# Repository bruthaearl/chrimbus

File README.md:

# chrimbus
## chrimbus tree ornamets for the family

More details on my [blog](http://www.oakst.io)

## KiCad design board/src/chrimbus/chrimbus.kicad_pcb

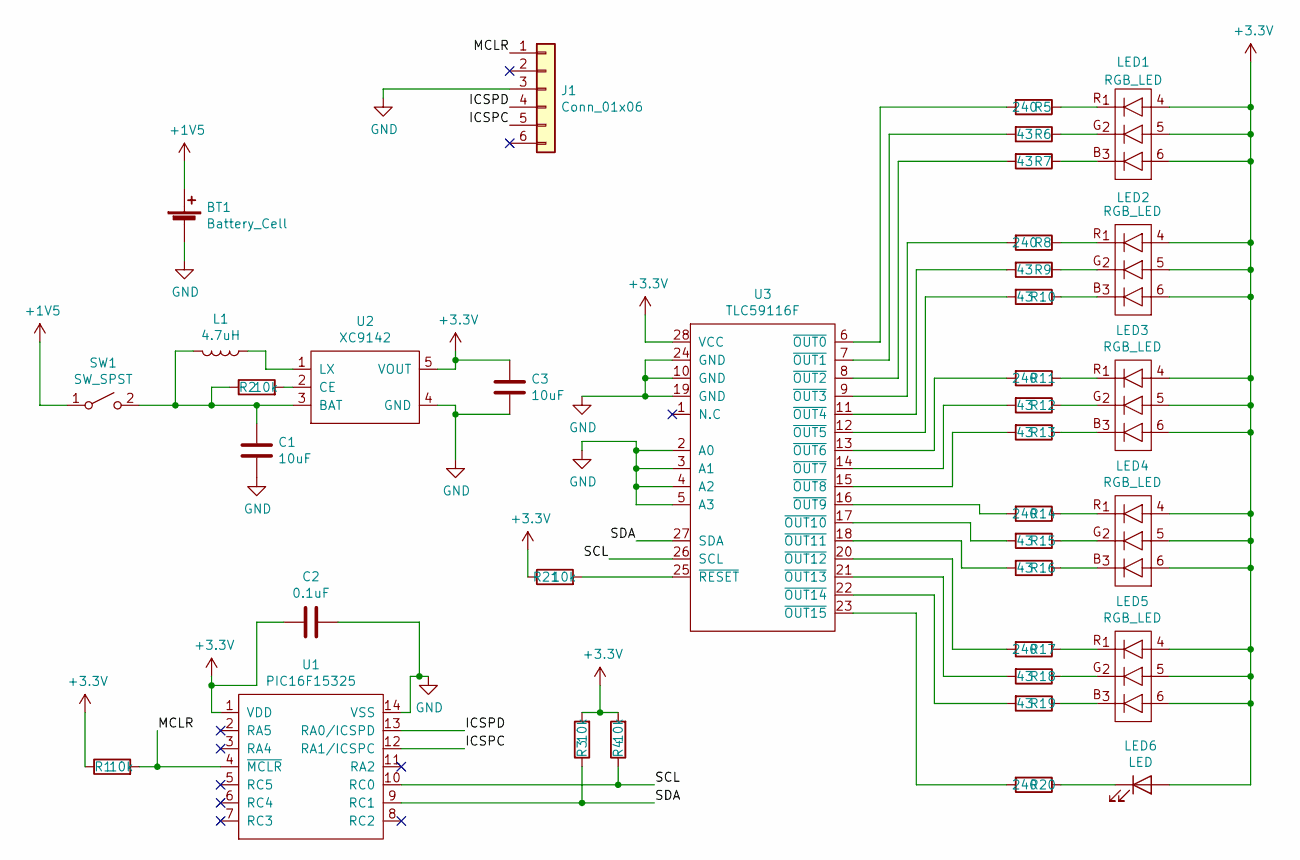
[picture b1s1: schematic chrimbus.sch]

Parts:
BT1: Battery_Cell; BCAAAPC
C1, C3: 10uF; C_0805_2012Metric
C2: 0.1uF; C_0805_2012Metric
J1: Conn_01x06; Tag Connect
L1: 4.7uH; L_0805_2012Metric_Pad1.15x1.40mm_HandSolder
LED1, LED2, LED3, LED4, LED5: RGB_LED; APF3236LSEEZGKQBKC
LED6: LED; LTST-C150AKT
R1, R2, R3, R4, R21: 10k; R_0603_1608Metric
R5, R8, R11, R14, R17, R20: 240; R_0603_1608Metric
R6, R7, R9, R10, R12, R13, R15, R16, R18, R19: 43; R_0603_1608Metric
SW1: SW_SPST; GF-123-0054
U1: PIC16F15325; TSSOP-14_4.4x5mm_P0.65mm
U2: XC9142; SOT-23-5_HandSoldering
U3: TLC59116F; TSSOP-28_4.4x9.7mm_P0.65mm

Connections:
+1V5: BT1.1 (+), SW1.1 (A)
+3V3: C2.2, C3.2, LED1.4, LED1.5, LED1.6, LED2.4, LED2.5, LED2.6, LED3.4, LED3.5, LED3.6, LED4.4, LED4.5, LED4.6, LED5.4, LED5.5, LED5.6, LED6.2 (A), R1.1, R3.2, R4.2, R21.1, U1.1 (VDD), U2.5 (VOUT), U3.28 (VCC); also elsewhere on the board
/ICSPC: J1.5, U1.12 (RA1/ICSPC)
/ICSPD: J1.4, U1.13 (RA0/ICSPD)
/MCLR: J1.1, R1.2, U1.4 (~MCLR)
/SCL: R4.1, U1.10 (RC0), U3.26 (SCL)
/SDA: R3.1, U1.9 (RC1), U3.27 (SDA)
GND: BT1.2 (-), C1.1, C2.1, C3.1, J1.3, U1.14 (VSS), U2.4 (GND), U3.2 (A0), U3.3 (A1), U3.4 (A2), U3.5 (A3), U3.10 (GND), U3.19 (GND), U3.24 (GND); also elsewhere on the board
unnamed: C1.2, L1.2, R2.1, SW1.2 (B), U2.3 (BAT)
unnamed: L1.1, U2.1 (LX)
unnamed: LED1.1, R5.1
unnamed: LED1.2, R6.1
unnamed: LED1.3, R7.1
unnamed: LED2.1, R8.1
unnamed: LED2.2, R9.1
unnamed: LED2.3, R10.1
unnamed: LED3.1, R11.1
unnamed: LED3.2, R12.1
unnamed: LED3.3, R13.1
unnamed: LED4.1, R14.1
unnamed: LED4.2, R15.1
unnamed: LED4.3, R16.1
unnamed: LED5.1, R17.1
unnamed: LED5.2, R18.1
unnamed: LED5.3, R19.1
unnamed: LED6.1 (K), R20.1
unnamed: R2.2, U2.2 (CE)
unnamed: R5.2, U3.6 (~OUT0)
unnamed: R6.2, U3.7 (~OUT1)
unnamed: R7.2, U3.8 (~OUT2)
unnamed: R8.2, U3.9 (~OUT3)
unnamed: R9.2, U3.11 (~OUT4)
unnamed: R10.2, U3.12 (~OUT5)
unnamed: R11.2, U3.13 (~OUT6)
unnamed: R12.2, U3.14 (~OUT7)
unnamed: R13.2, U3.15 (~OUT8)
unnamed: R14.2, U3.16 (~OUT9)
unnamed: R15.2, U3.17 (~OUT10)
unnamed: R16.2, U3.18 (~OUT11)
unnamed: R17.2, U3.20 (~OUT12)
unnamed: R18.2, U3.21 (~OUT13)
unnamed: R19.2, U3.22 (~OUT14)
unnamed: R20.2, U3.23 (~OUT15)
unnamed: R21.2, U3.25 (~RESET)

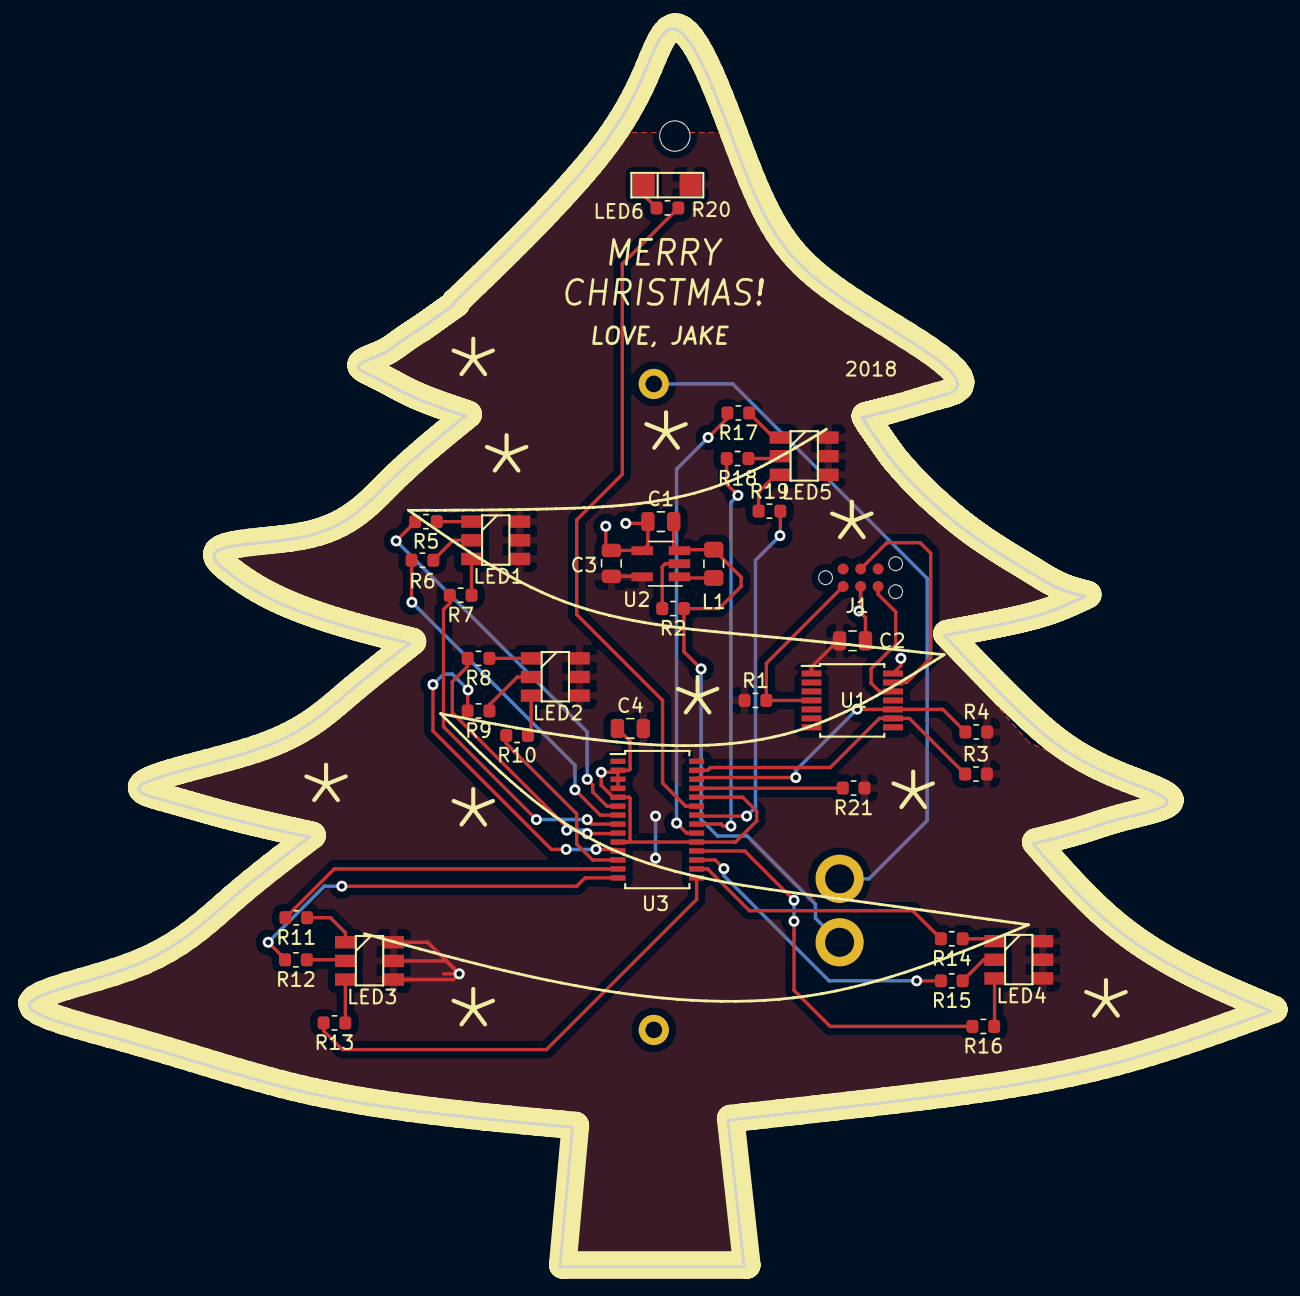
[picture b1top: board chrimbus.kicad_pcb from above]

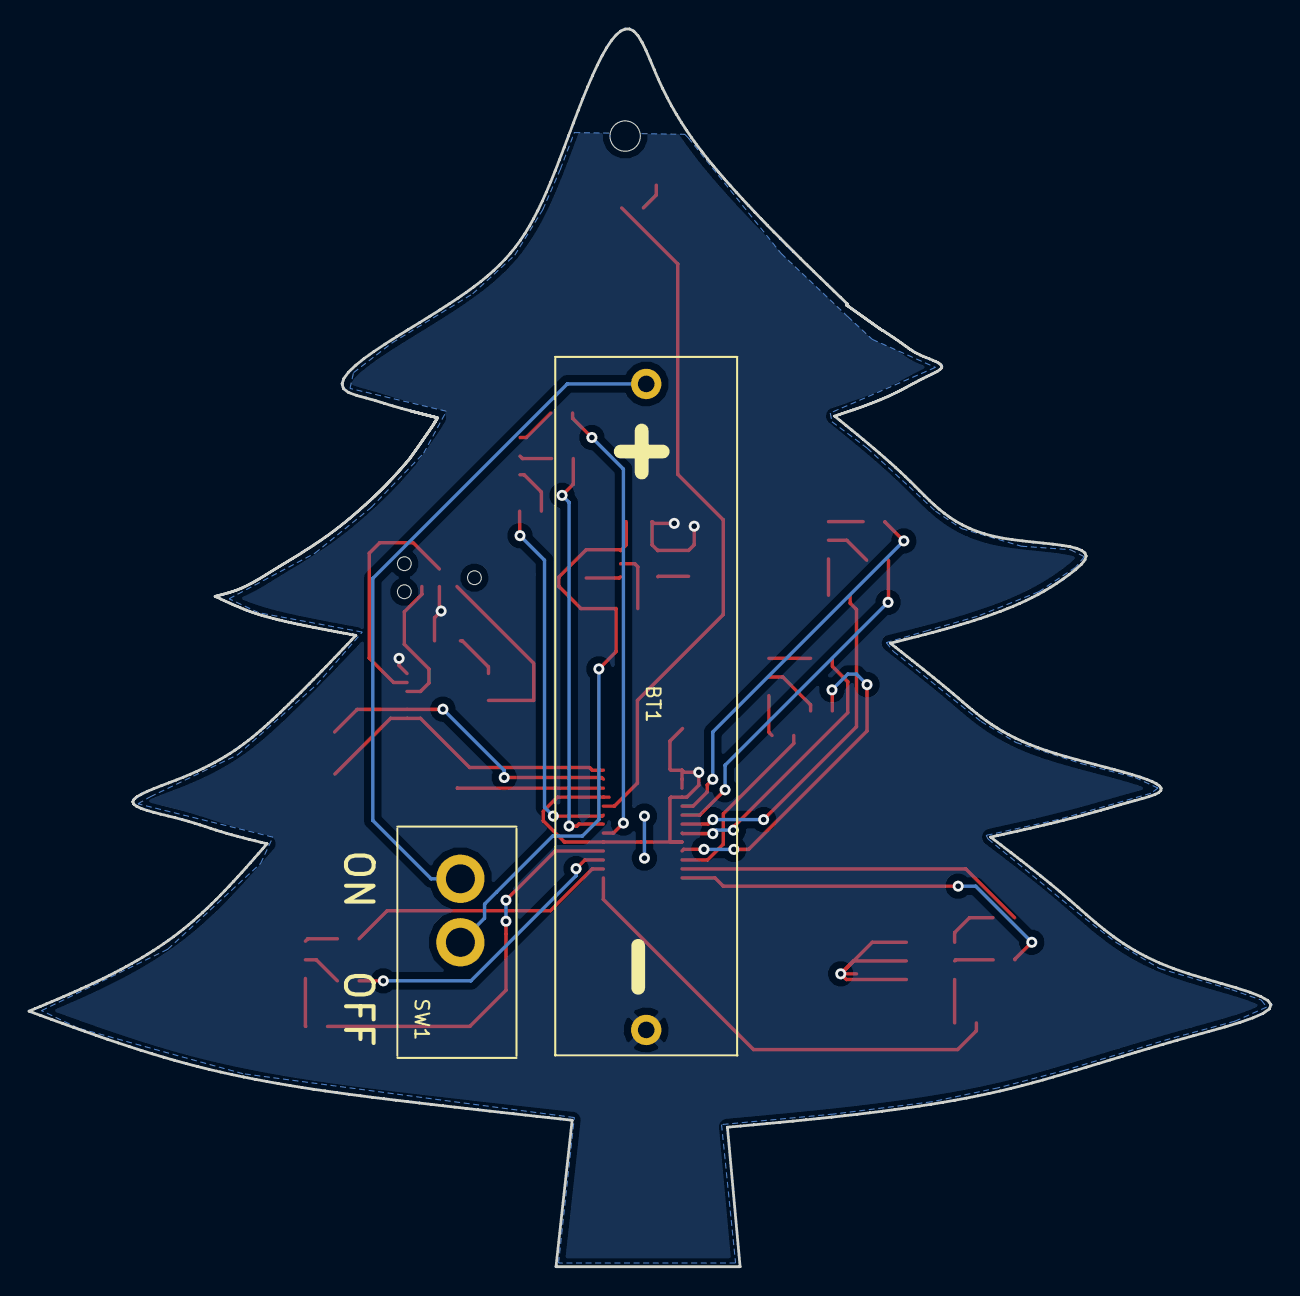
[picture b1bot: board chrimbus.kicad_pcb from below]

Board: 2 copper layers, 90.0 x 89.7 mm, 39 parts (2 on the bottom side), 44 nets.

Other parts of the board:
C4: 0.1uF; C_0805_2012Metric
MH1: MountingHole; MountingHole_2.2mm_M2

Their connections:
+3V3: C4.2; also elsewhere on the board
GND: C4.1; also elsewhere on the board

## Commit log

2018-11-18 buildup
2018-11-21 schematic done
2018-11-26 last commit before dev branch
2018-11-30 led flash code cleanup
2018-12-16 dev final commit
2018-12-16 git cleanup
